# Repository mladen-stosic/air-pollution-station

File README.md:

# air-pollution-station
Arduino project

### Hardware used:
WeMos D1 Mini(ESP8266), PMSA003, BME280

### Project description:
Gather data from PMS and BME sensors and send them to opensensemap.org

### Implemetation:
After reset wake up PMS sensor, put it in passive mode. Try to connect to WiFi, if connection fails go to low power mode for 2 minutes.
When connected, wait 30 seconds for PMS Sensor to start sending valid values. Gather 4 different measurements from it and get their average value. This is done to increase accuracy. Gather data from BME Sensor. Send all gathered values to opensensemap.org server. Put PMS sensor to sleep. Enter deep sleep for 3 minutes, when MCU will be reset by internal clock pulling it's RST pin to GND.

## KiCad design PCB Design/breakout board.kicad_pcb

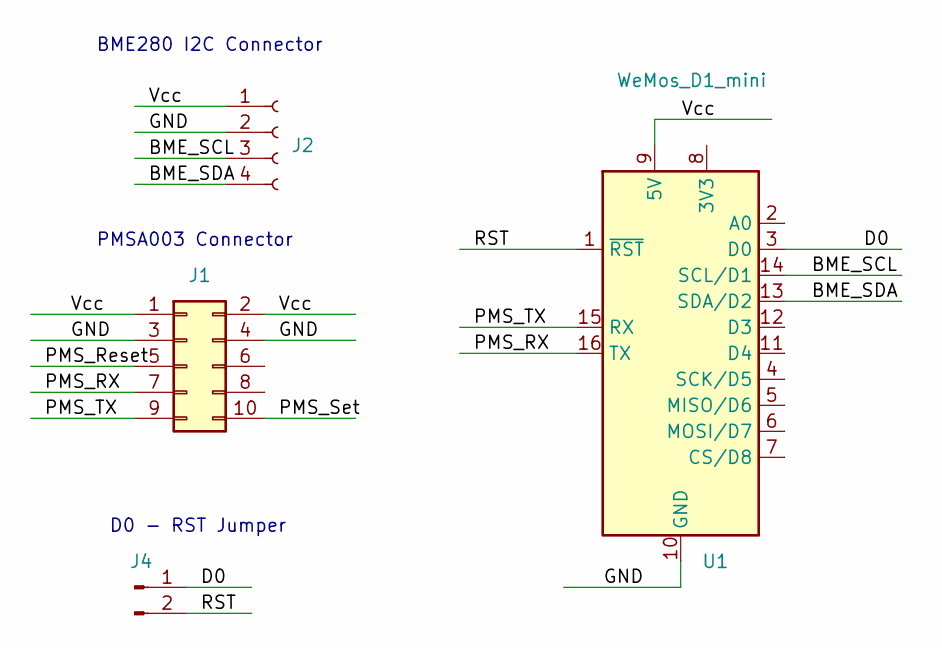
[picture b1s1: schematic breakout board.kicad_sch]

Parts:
J1: Conn_02x05_Odd_Even; PinHeader_2x05_P1.27mm_Vertical_SMD
J2: Conn_01x04_Female; PinHeader_1x04_P2.54mm_Vertical
J4: Conn_01x02_Male; PinHeader_1x02_P2.54mm_Vertical
U1: WeMos_D1_mini; WEMOS_D1_mini_light

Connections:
/BME_SCL: J2.3, U1.14 (SCL/D1)
/BME_SDA: J2.4, U1.13 (SDA/D2)
/D0: J4.1, U1.3 (D0)
/GND: J1.3, J1.4, J2.2, U1.10 (GND)
/PMS_RX: J1.7, U1.16 (TX)
/PMS_Reset: J1.5
/PMS_Set: J1.10
/PMS_TX: J1.9, U1.15 (RX)
/RST: J4.2, U1.1 (~RST)
/Vcc: J1.1, J1.2, J2.1, U1.9 (5V)

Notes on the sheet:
BME280 I2C Connector
PMSA003 Connector
D0 - RST Jumper

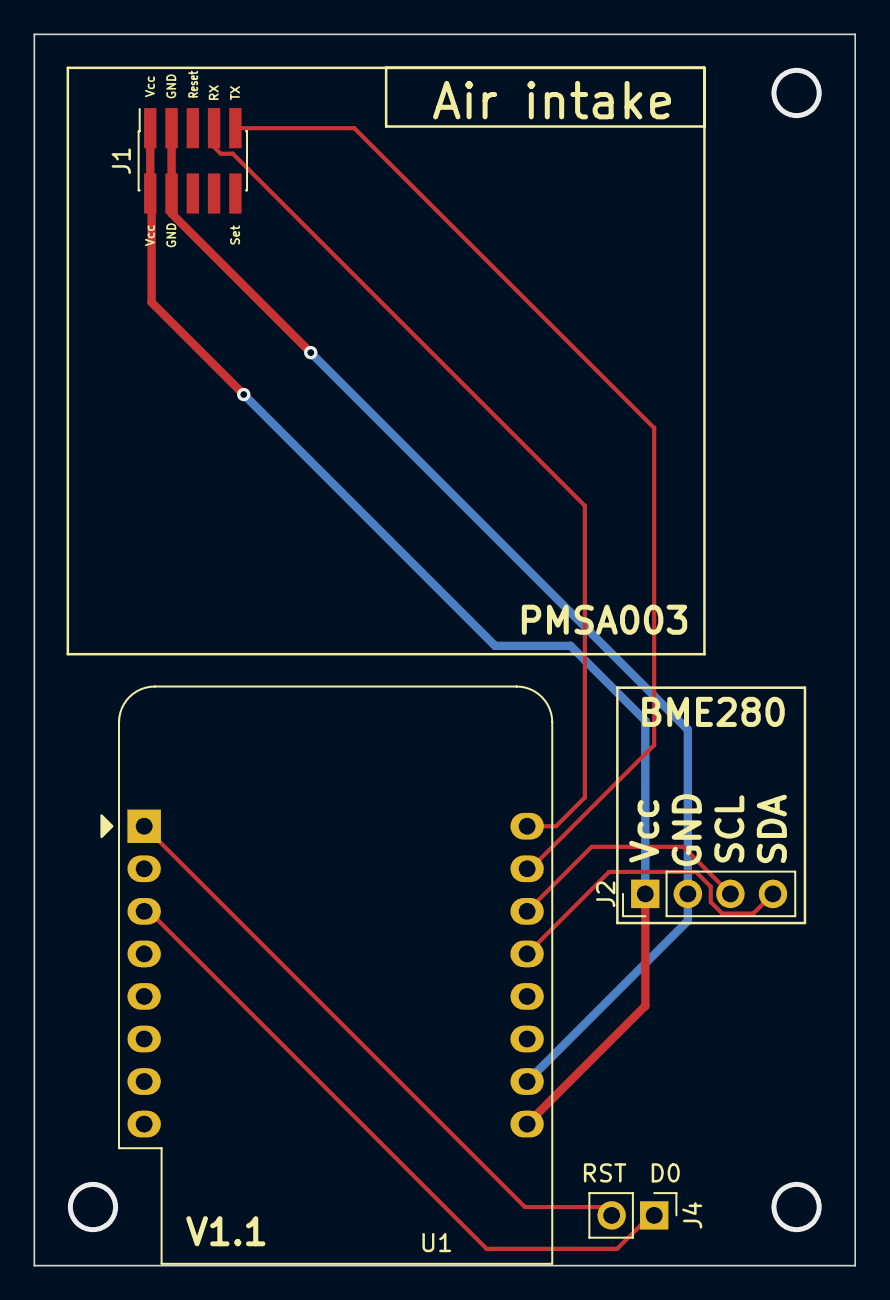
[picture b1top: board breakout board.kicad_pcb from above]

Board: 2 copper layers, 49.0 x 73.5 mm, 4 parts (0 on the bottom side), 8 nets.

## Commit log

2022-11-03 add pcb design files - KiCad project
